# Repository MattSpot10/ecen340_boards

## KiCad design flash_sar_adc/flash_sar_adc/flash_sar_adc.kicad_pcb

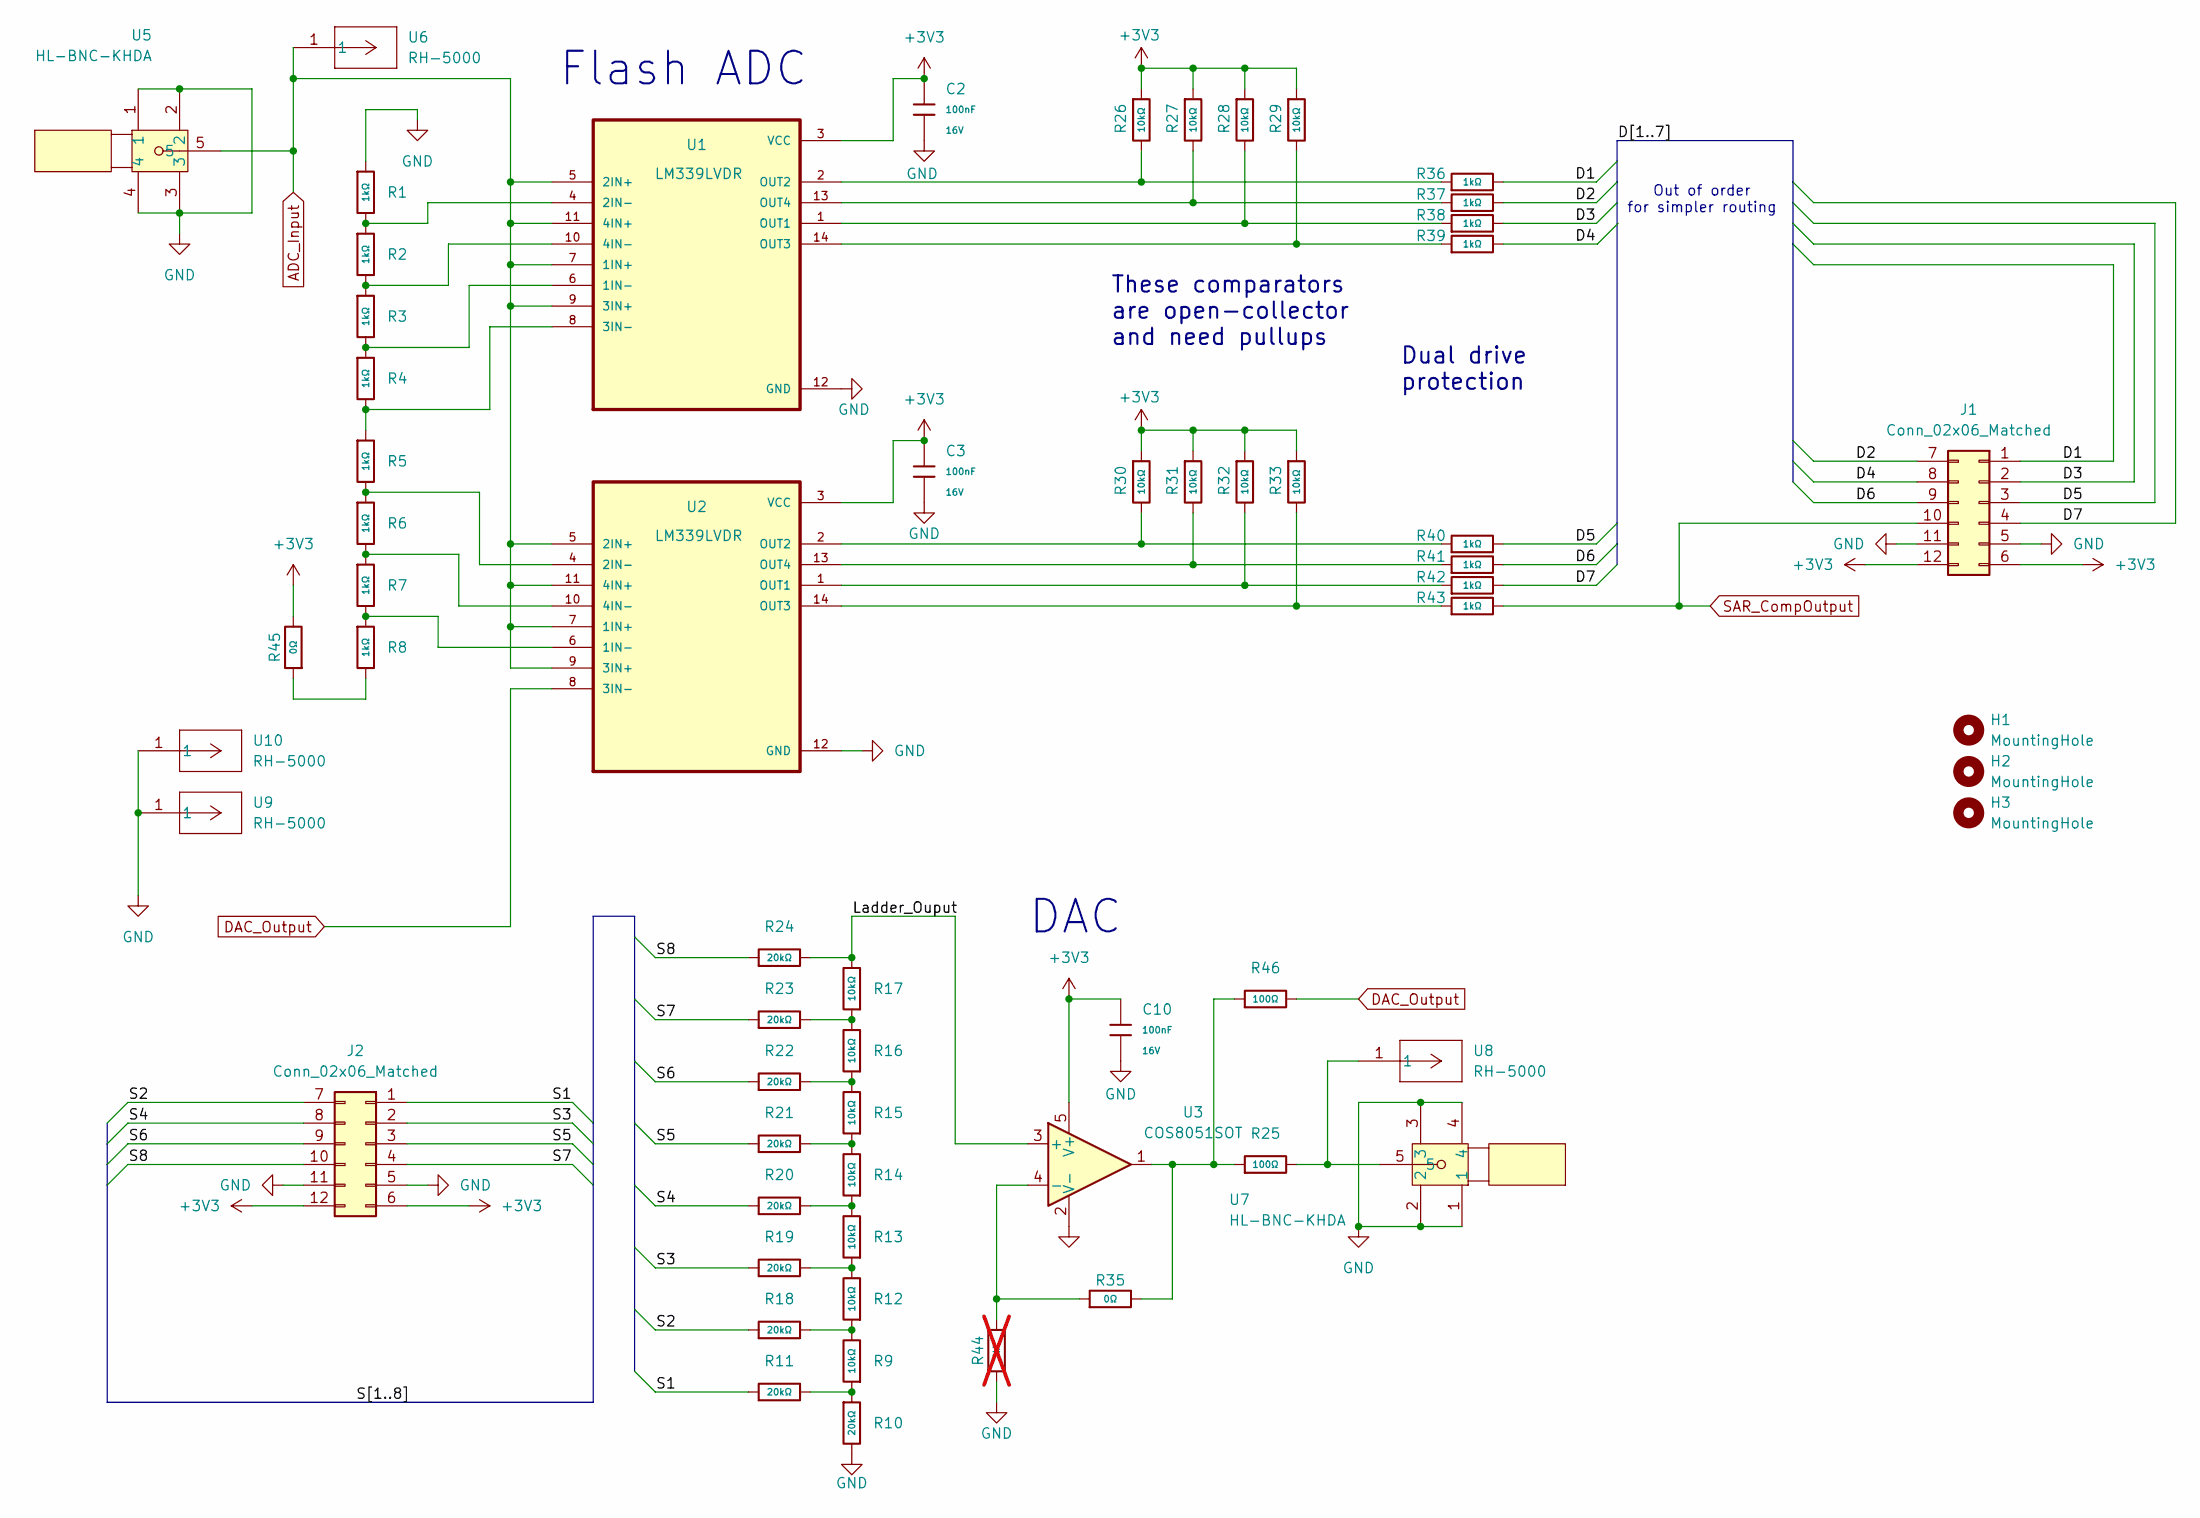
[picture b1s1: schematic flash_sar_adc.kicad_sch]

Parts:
C2, C3, C10: 100nF; C_0402; Voltage Rated 16V; Tolerance ±10%; Part CL05B104KO5NNNC; LCSC C1525
H1, H2, H3: MountingHole; MountingHole_3.5mm
J1, J2: Conn_02x06_Matched; PinHeader_2x06_P2.54mm_Vertical; LCSC C5383091
R1, R2, R3, R4, R5, R6, R7, R8, R36, R37, R38, R39, R40, R41, R42, R43: 1kΩ; R_0402; Overload Voltage (Max) 50V; Tolerance ±1%; Part 0402WGF1001TCE; LCSC C11702
R9, R12, R13, R14, R15, R16, R17, R26, R27, R28, R29, R30, R31, R32, R33: 10kΩ; R_0402; Overload Voltage (Max) 50V; Tolerance ±1%; Part 0402WGF1002TCE; LCSC C25744
R10, R11, R18, R19, R20, R21, R22, R23, R24: 20kΩ; R_0402; Overload Voltage (Max) 50V; Tolerance ±1%; Part 0402WGF2002TCE; LCSC C25765
R25, R46: 100Ω; R_0402; Overload Voltage (Max) 50V; Tolerance ±1%; Part 0402WGF1000TCE; LCSC C25076
R35, R45: 0Ω; R_0402; Overload Voltage (Max) 50V; Tolerance ±1%; Part 0402WGF0000TCE; LCSC C17168
R44: NA; R_0402; not fitted
U1, U2: LM339LVDR; SOIC127P600X175-14N; LCSC C22427665
U3: COS8051SOT; SOT-23-5; LCSC C7463385
U5, U7: HL-BNC-KHDA; BNC-TH_L12.0-W12.0; LCSC Part C19712152
U6, U8, U9, U10: RH-5000; CONN1_1514-2_KEY; Mouser Part Number 534-1514-2

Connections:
+3V3: C2.1, C3.1, C10.1, J1.6, J1.12, J2.6, J2.12, R26.1, R27.1, R28.1, R29.1, R30.1, R31.1, R32.1, R33.1, R45.2, U1.3 (VCC), U2.3 (VCC), U3.5 (V+)
/D1: J1.1, R36.2
/D2: J1.7, R37.2
/D3: J1.2, R38.2
/D4: J1.8, R39.2
/D5: J1.3, R40.2
/D6: J1.9, R41.2
/D7: J1.4, R42.2
/Ladder_Ouput: R17.2, R24.2, U3.3 (+)
/S1: J2.1, R11.1
/S2: J2.7, R18.1
/S3: J2.2, R19.1
/S4: J2.8, R20.1
/S5: J2.3, R21.1
/S6: J2.9, R22.1
/S7: J2.4, R23.1
/S8: J2.10, R24.1
ADC_Input: U1.5 (2IN+), U1.7 (1IN+), U1.9 (3IN+), U1.11 (4IN+), U2.5 (2IN+), U2.7 (1IN+), U2.9 (3IN+), U2.11 (4IN+), U5.5, U6.1
DAC_Output: R46.2, U2.8 (3IN-)
GND: C2.2, C3.2, C10.2, J1.5, J1.11, J2.5, J2.11, R1.1, R10.2, R44.1, U1.12 (GND), U2.12 (GND), U3.2 (V-), U5.1, U5.2, U5.3, U5.4, U7.1, U7.2, U7.3, U7.4, U9.1, U10.1
unnamed: R9.1, R10.1, R11.2
unnamed: R9.2, R12.1, R18.2
unnamed: R12.2, R13.1, R19.2
unnamed: R13.2, R14.1, R20.2
unnamed: R14.2, R15.1, R21.2
unnamed: R15.2, R16.1, R22.2
unnamed: R16.2, R17.1, R23.2
unnamed: R25.1, R35.2, R46.1, U3.1
unnamed: R25.2, U7.5, U8.1
unnamed: R8.2, R45.1
unnamed: R3.2, R4.1, U1.6 (1IN-)
unnamed: R1.2, R2.1, U1.4 (2IN-)
unnamed: R4.2, R5.1, U1.8 (3IN-)
unnamed: R2.2, R3.1, U1.10 (4IN-)
unnamed: R28.2, R38.1, U1.1 (OUT1)
unnamed: R26.2, R36.1, U1.2 (OUT2)
unnamed: R29.2, R39.1, U1.14 (OUT3)
unnamed: R27.2, R37.1, U1.13 (OUT4)
unnamed: R7.2, R8.1, U2.6 (1IN-)
unnamed: R5.2, R6.1, U2.4 (2IN-)
unnamed: R6.2, R7.1, U2.10 (4IN-)
unnamed: R32.2, R42.1, U2.1 (OUT1)
unnamed: R30.2, R40.1, U2.2 (OUT2)
unnamed: R33.2, R43.1, U2.14 (OUT3)
unnamed: R31.2, R41.1, U2.13 (OUT4)
unnamed: R35.1, R44.2, U3.4 (-)
SAR_CompOutput: J1.10, R43.2

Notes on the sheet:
DAC
Dual drive protection
Out of order for simpler routing
Flash ADC
These comparators are open-collector and need pullups

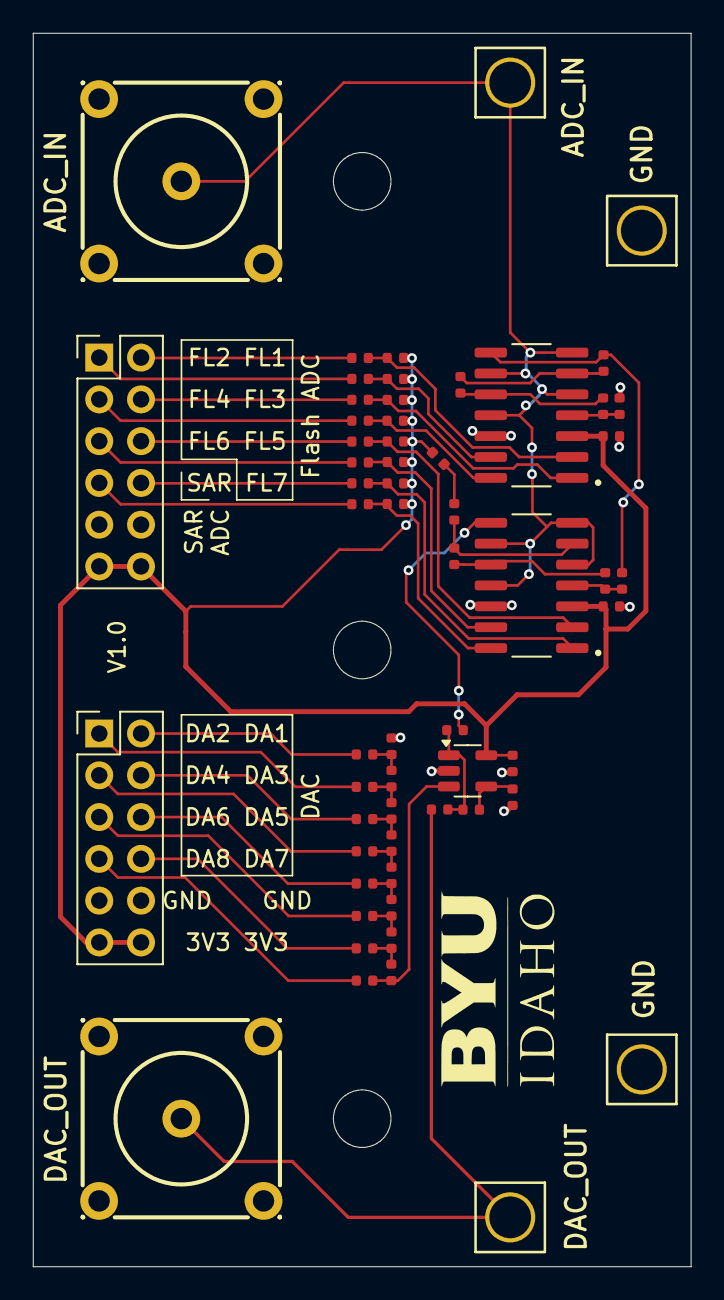
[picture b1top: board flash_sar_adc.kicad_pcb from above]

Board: 2 copper layers, 40.0 x 75.0 mm, 62 parts (0 on the bottom side), 47 nets.

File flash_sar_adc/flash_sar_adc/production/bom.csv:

Designator,Footprint,Quantity,Value,LCSC Part #
"C10, C2, C3",C_0402,3,100nF,C1525
"J1, J2",PinHeader_2x06_P2.54mm_Vertical,2,Conn_02x06_Matched,C5383091
"R1, R2, R3, R36, R37, R38, R39, R4, R40, R41, R42, R43, R5, R6, R7, R8",R_0402,16,1kΩ,C11702
"R10, R11, R18, R19, R20, R21, R22, R23, R24",R_0402,9,20kΩ,C25765
"R12, R13, R14, R15, R16, R17, R26, R27, R28, R29, R30, R31, R32, R33, R9",R_0402,15,10kΩ,C25744
"R25, R46",R_0402,2,100Ω,C25076
"R35, R45",R_0402,2,0Ω,C17168
"U1, U2",SOIC127P600X175-14N,2,LM339LVDR,C22427665
U3,SOT-23-5,1,OPA843xDBV,C7463385
"U5, U7",BNC-TH_L12.0-W12.0,2,HL-BNC-KHDA,C19712152

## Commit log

2026-01-24 finished initial schematic
2026-01-24 added Test Points
2026-01-24 fixed loc
2026-04-07 finished flash/sar adc board
2026-04-07 added gerbers
2026-04-07 fixed power supply errors
2026-04-07 fixed bom errors
2026-04-07 added version number
2026-04-08 fixed a few more silkscreen errors
